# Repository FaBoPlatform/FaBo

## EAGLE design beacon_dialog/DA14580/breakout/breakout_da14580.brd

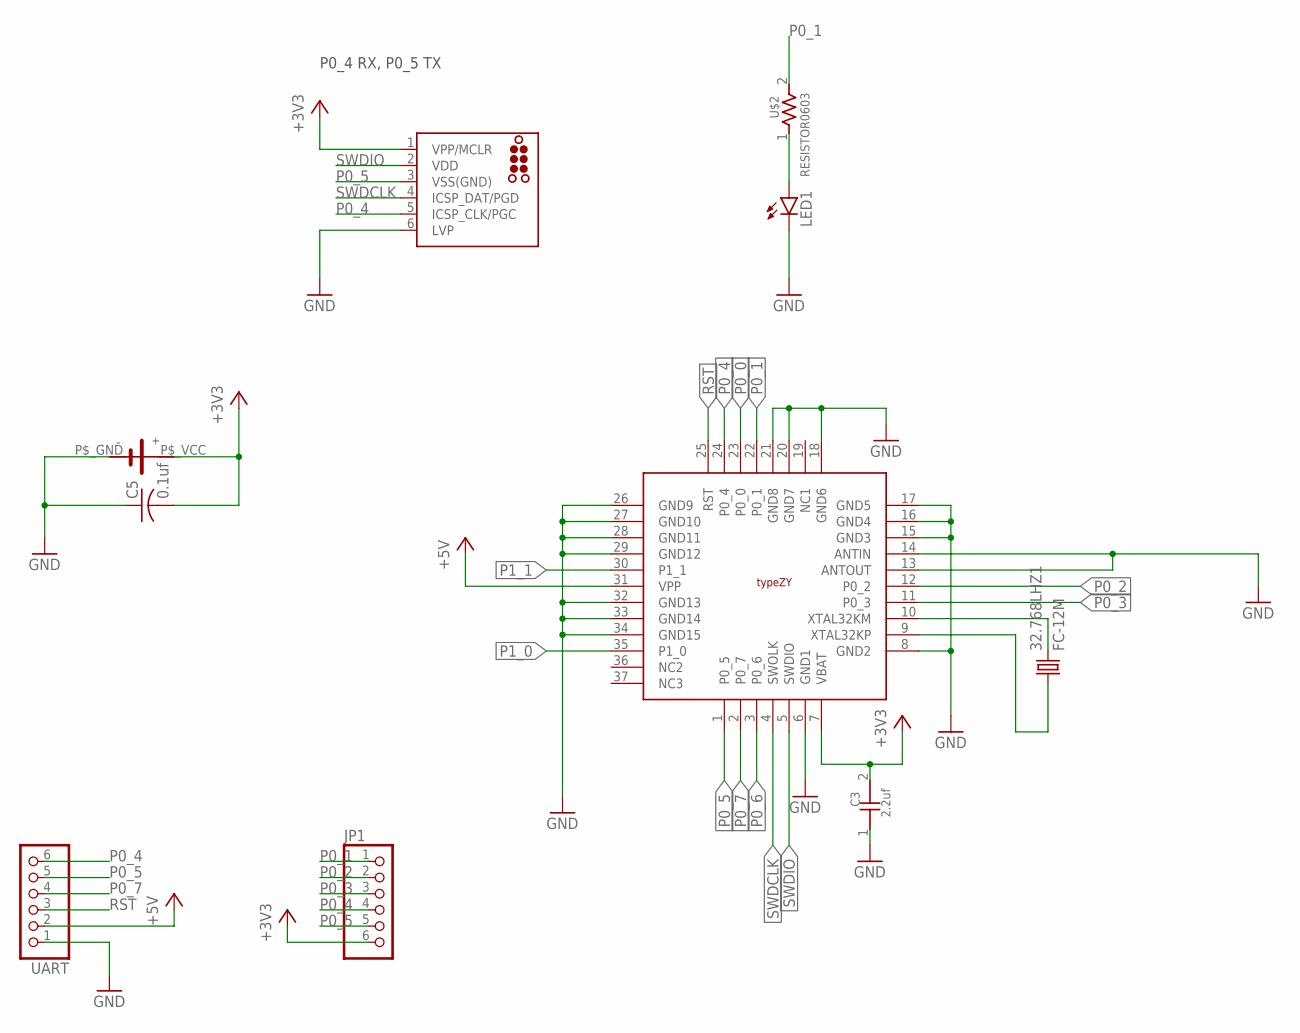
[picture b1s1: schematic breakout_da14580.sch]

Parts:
32.768LHZ1: FC-12M
C3: 2.2uf; 0603
C5: 0.1uf; C0603
J1: TC2030-MCP
JP1: PINHD-1X6; 1X06
LED1: LED-EIA0603; EIA0603-LED
U$1: MURATA-TYPEZY; MURATA_TYPEZY
U$2: RESISTOR0603; 0603
U$3: SMTU2450-BOTTOM-MINI
UART: PINHD-1X6; 1X06

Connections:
+3V3: C3.2, C5.2, J1.1 (VPP/MCLR), JP1.6, U$1.7 (VBAT), U$3.P$_VCC
+5V: U$1.31 (VPP), UART.2
GND: C3.1, C5.1, J1.6 (LVP), LED1.C, U$1.6 (GND1), U$1.8 (GND2), U$1.13 (ANTOUT), U$1.14 (ANTIN), U$1.15 (GND3), U$1.16 (GND4), U$1.17 (GND5), U$1.18 (GND6), U$1.20 (GND7), U$1.21 (GND8), U$1.26 (GND9), U$1.27 (GND10), U$1.28 (GND11), U$1.29 (GND12), U$1.32 (GND13), U$1.33 (GND14), U$1.34 (GND15), U$3.P$_GND, UART.1
unnamed: LED1.A, U$2.1
P0_0: U$1.23 (P0_0)
P0_1: JP1.1, U$1.22 (P0_1), U$2.2
P0_2: JP1.2, U$1.12 (P0_2)
P0_3: JP1.3, U$1.11 (P0_3)
P0_4: J1.5 (ICSP_CLK/PGC), JP1.4, U$1.24 (P0_4), UART.6
P0_5: J1.3 (VSS(GND)), JP1.5, U$1.1 (P0_5), UART.5
P0_6: U$1.3 (P0_6)
P0_7: U$1.2 (P0_7), UART.4
P1_0: U$1.35 (P1_0)
P1_1: U$1.30 (P1_1)
RST: U$1.25 (RST), UART.3
SWDCLK: J1.4 (ICSP_DAT/PGD), U$1.4 (SWOLK)
SWDIO: J1.2 (VDD), U$1.5 (SWDIO)
XTAL32KM: 32.768LHZ1.2, U$1.10 (XTAL32KM)
XTAL32KP: 32.768LHZ1.1, U$1.9 (XTAL32KP)

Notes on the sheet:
P0_4 RX, P0_5 TX

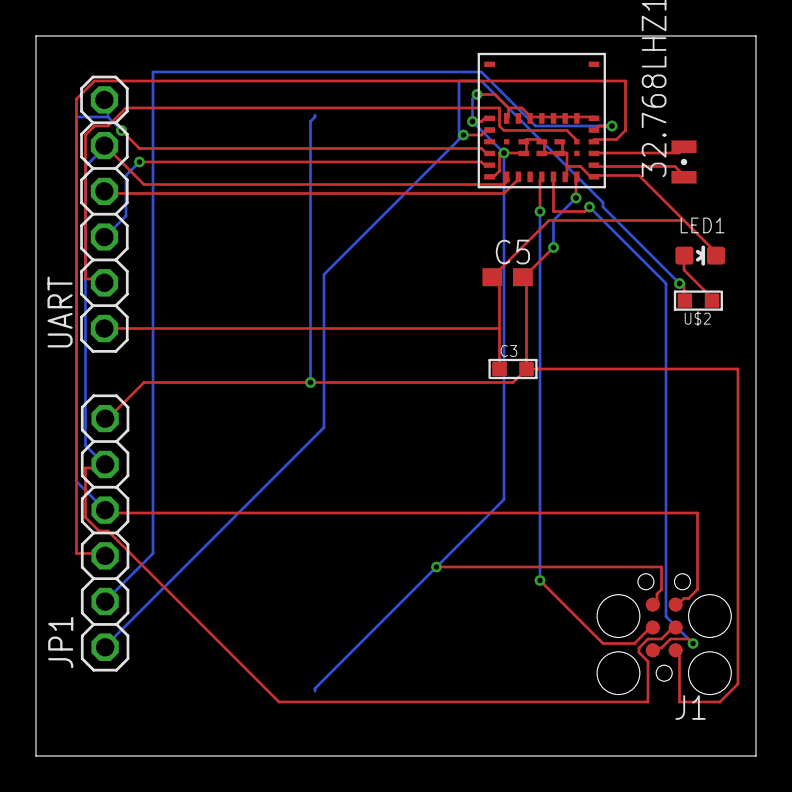
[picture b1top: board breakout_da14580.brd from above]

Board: 2 copper layers, 40.0 x 40.0 mm, 10 parts (0 on the bottom side), 15 nets.

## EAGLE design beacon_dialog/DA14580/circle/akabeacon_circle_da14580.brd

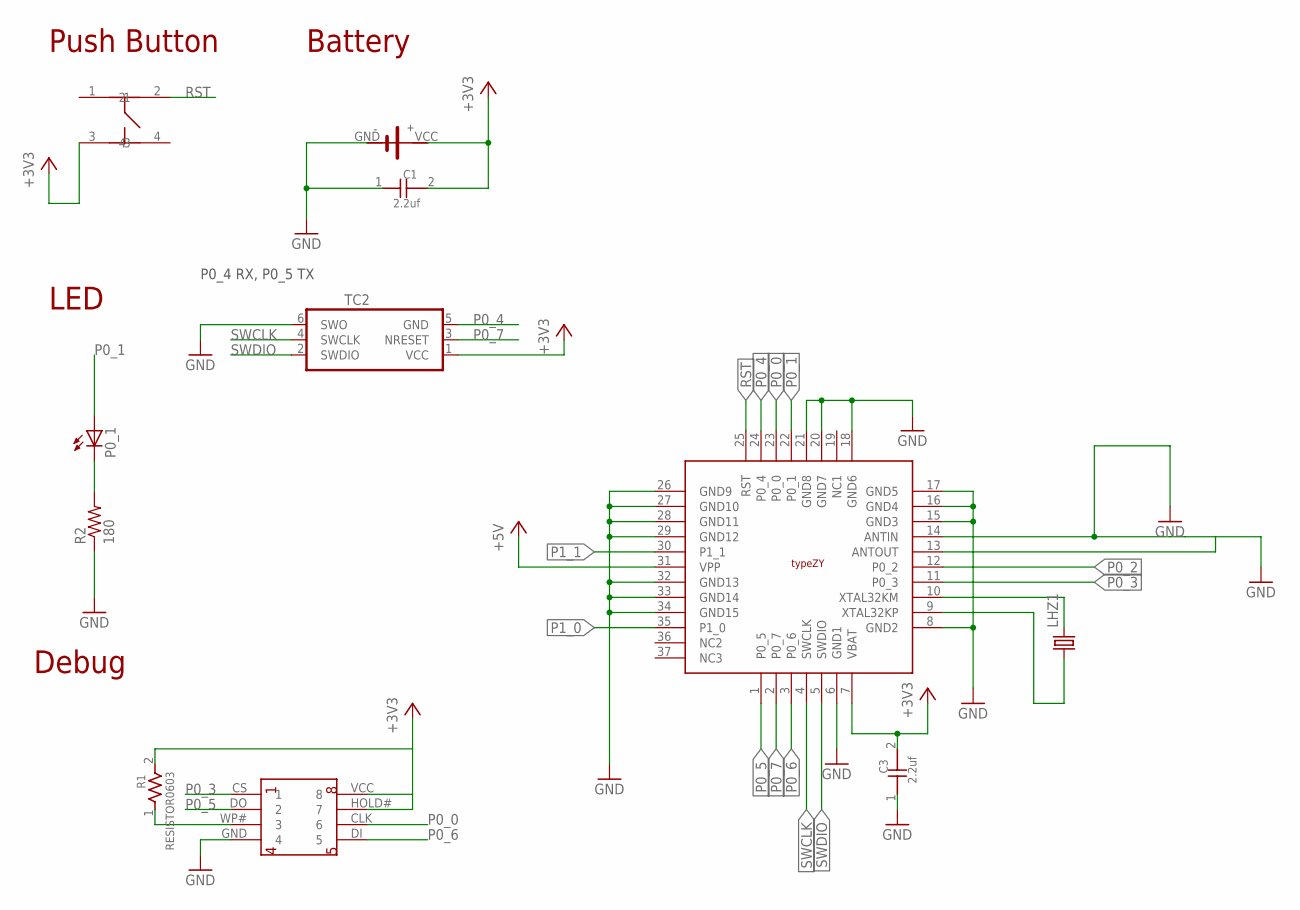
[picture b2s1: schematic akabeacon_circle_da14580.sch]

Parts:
C1, C3: 2.2uf; 0603
LHZ1: FC-12M
P0_1: LEDCHIP-LED0603; CHIP-LED0603
R1: RESISTOR0603; 0603
R2: 180; 0603-RES
TC2: TC2030-IDC-NL
U$1: MURATA-TYPEZY; MURATA_TYPEZY
U$3: CIRCLE-TYPE1; CIRCLE-TYE1-TC2030
U$5: FLASH-MEMORY-2M(WINBOND)
U$7: SWICTH-4P(KMR2); SWITCH-4P(KMR2)

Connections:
+3V3: C1.2, C3.2, R1.2, TC2.1 (VCC), U$1.7 (VBAT), U$3.VCC, U$5.HOLD# (7), U$5.VCC (8), U$7.3
+5V: U$1.31 (VPP)
GND: C1.1, C3.1, R2.1, TC2.6 (SWO), U$1.6 (GND1), U$1.8 (GND2), U$1.14 (ANTIN), U$1.15 (GND3), U$1.16 (GND4), U$1.17 (GND5), U$1.18 (GND6), U$1.20 (GND7), U$1.21 (GND8), U$1.26 (GND9), U$1.27 (GND10), U$1.28 (GND11), U$1.29 (GND12), U$1.32 (GND13), U$1.33 (GND14), U$1.34 (GND15), U$3.GND, U$5.GND (4)
LED1: P0_1.C, R2.2
unnamed: R1.1, U$5.WP# (3)
P0_0: U$1.23 (P0_0), U$5.CLK (6)
P0_1: P0_1.A, U$1.22 (P0_1)
P0_2: U$1.12 (P0_2)
P0_3: U$1.11 (P0_3), U$5.CS (1)
P0_4: TC2.5 (GND), U$1.24 (P0_4)
P0_5: U$1.1 (P0_5), U$5.DO (2)
P0_6: U$1.3 (P0_6), U$5.DI (5)
P0_7: TC2.3 (NRESET), U$1.2 (P0_7)
P1_0: U$1.35 (P1_0)
P1_1: U$1.30 (P1_1)
RST: U$1.25 (RST), U$7.2
SWCLK: TC2.4 (SWCLK), U$1.4 (SWCLK)
SWDIO: TC2.2 (SWDIO), U$1.5 (SWDIO)
XTAL32KM: LHZ1.2, U$1.10 (XTAL32KM)
XTAL32KP: LHZ1.1, U$1.9 (XTAL32KP)

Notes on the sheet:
Battery
Push Button
Debug
LED
P0_4 RX, P0_5 TX

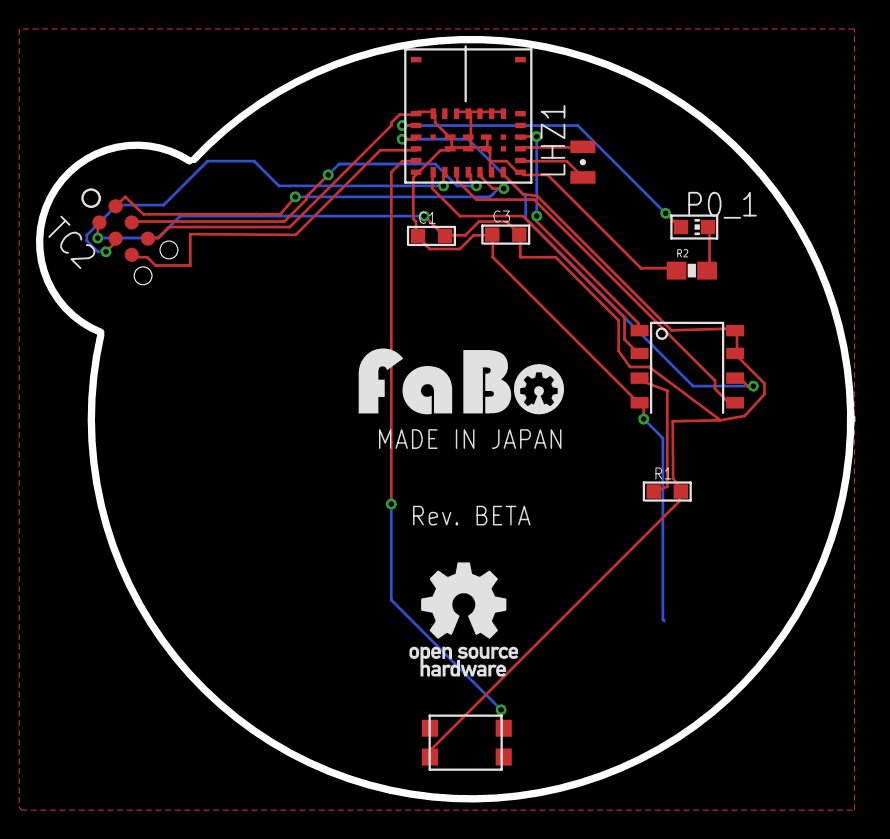
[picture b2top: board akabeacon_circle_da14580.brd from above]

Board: 2 copper layers, 13 parts (0 on the bottom side), 16 nets.

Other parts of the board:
U$2: LOGO_FABO_M
U$6: LOGO_OSHW_T_M

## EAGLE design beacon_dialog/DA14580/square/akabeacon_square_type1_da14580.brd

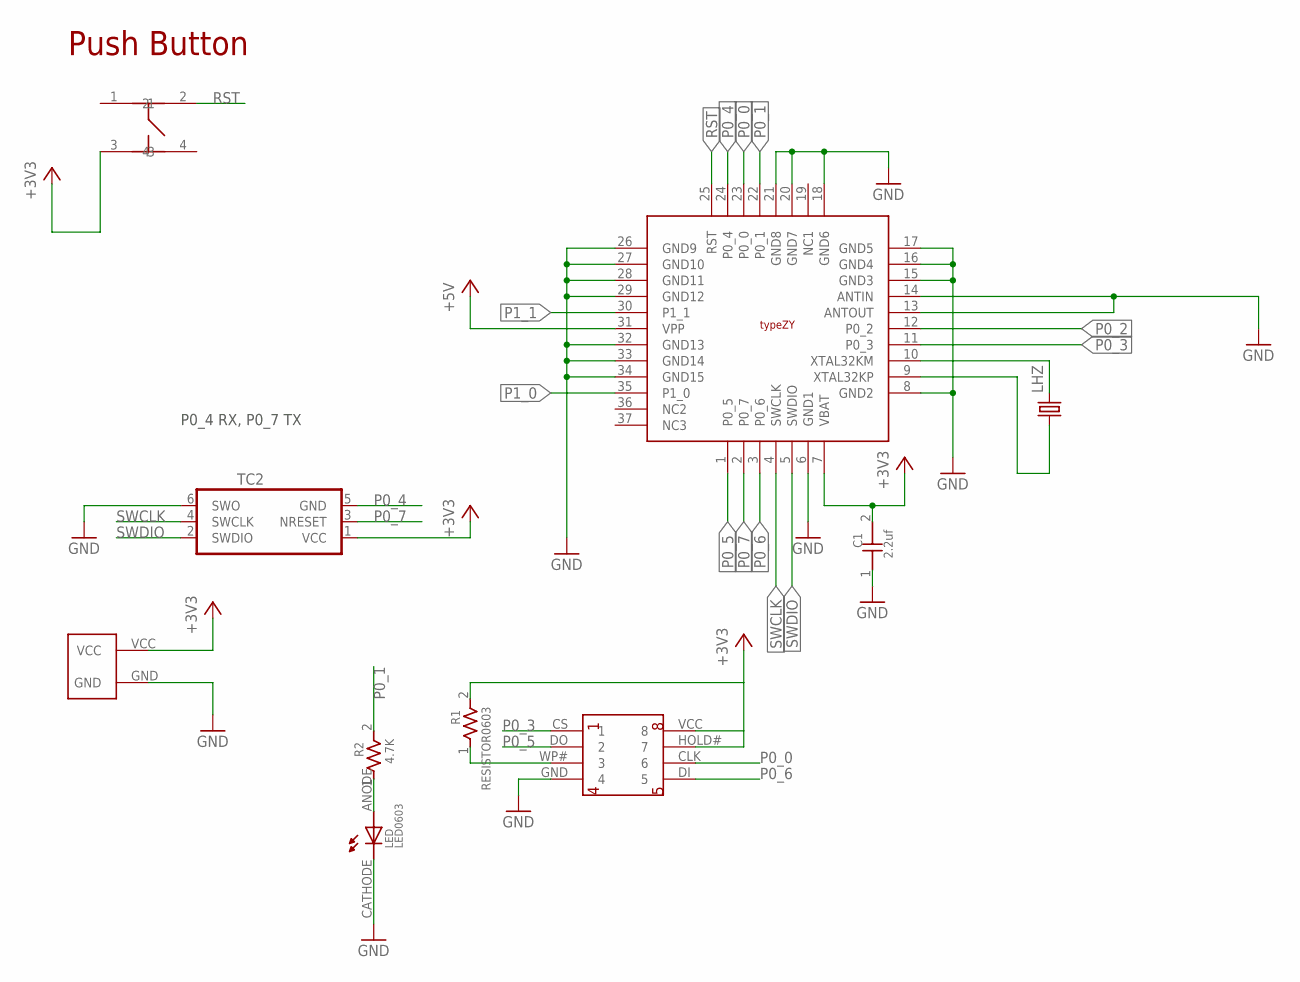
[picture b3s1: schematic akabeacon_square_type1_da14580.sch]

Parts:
C1: 2.2uf; 0603
LED: LED0603; 0603
LHZ: FC-12M
R1: RESISTOR0603; 0603
R2: 4.7K; 0603
TC2: TC2030-IDC-NL
U$2: SQUARE-TYPE1; SQUARE-TYPE1-TC2030
U$3: FLASH-MEMORY-2M(WINBOND)
U$7: SWICTH-4P(KMR2); SWITCH-4P(KMR2)
U$9: MURATA-TYPEZY; MURATA_TYPEZY

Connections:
+3V3: C1.2, R1.2, TC2.1 (VCC), U$2.VCC, U$3.HOLD# (7), U$3.VCC (8), U$7.3, U$9.7 (VBAT)
+5V: U$9.31 (VPP)
GND: C1.1, LED.CATHODE, TC2.6 (SWO), U$2.GND, U$3.GND (4), U$9.6 (GND1), U$9.8 (GND2), U$9.13 (ANTOUT), U$9.14 (ANTIN), U$9.15 (GND3), U$9.16 (GND4), U$9.17 (GND5), U$9.18 (GND6), U$9.20 (GND7), U$9.21 (GND8), U$9.26 (GND9), U$9.27 (GND10), U$9.28 (GND11), U$9.29 (GND12), U$9.32 (GND13), U$9.33 (GND14), U$9.34 (GND15)
unnamed: R1.1, U$3.WP# (3)
unnamed: LED.ANODE, R2.1
P0_0: U$3.CLK (6), U$9.23 (P0_0)
P0_1: R2.2, U$9.22 (P0_1)
P0_2: U$9.12 (P0_2)
P0_3: U$3.CS (1), U$9.11 (P0_3)
P0_4: TC2.5 (GND), U$9.24 (P0_4)
P0_5: U$3.DO (2), U$9.1 (P0_5)
P0_6: U$3.DI (5), U$9.3 (P0_6)
P0_7: TC2.3 (NRESET), U$9.2 (P0_7)
P1_0: U$9.35 (P1_0)
P1_1: U$9.30 (P1_1)
RST: U$7.2, U$9.25 (RST)
SWCLK: TC2.4 (SWCLK), U$9.4 (SWCLK)
SWDIO: TC2.2 (SWDIO), U$9.5 (SWDIO)
XTAL32KM: LHZ.2, U$9.10 (XTAL32KM)
XTAL32KP: LHZ.1, U$9.9 (XTAL32KP)

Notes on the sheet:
Push Button
P0_4 RX, P0_7 TX

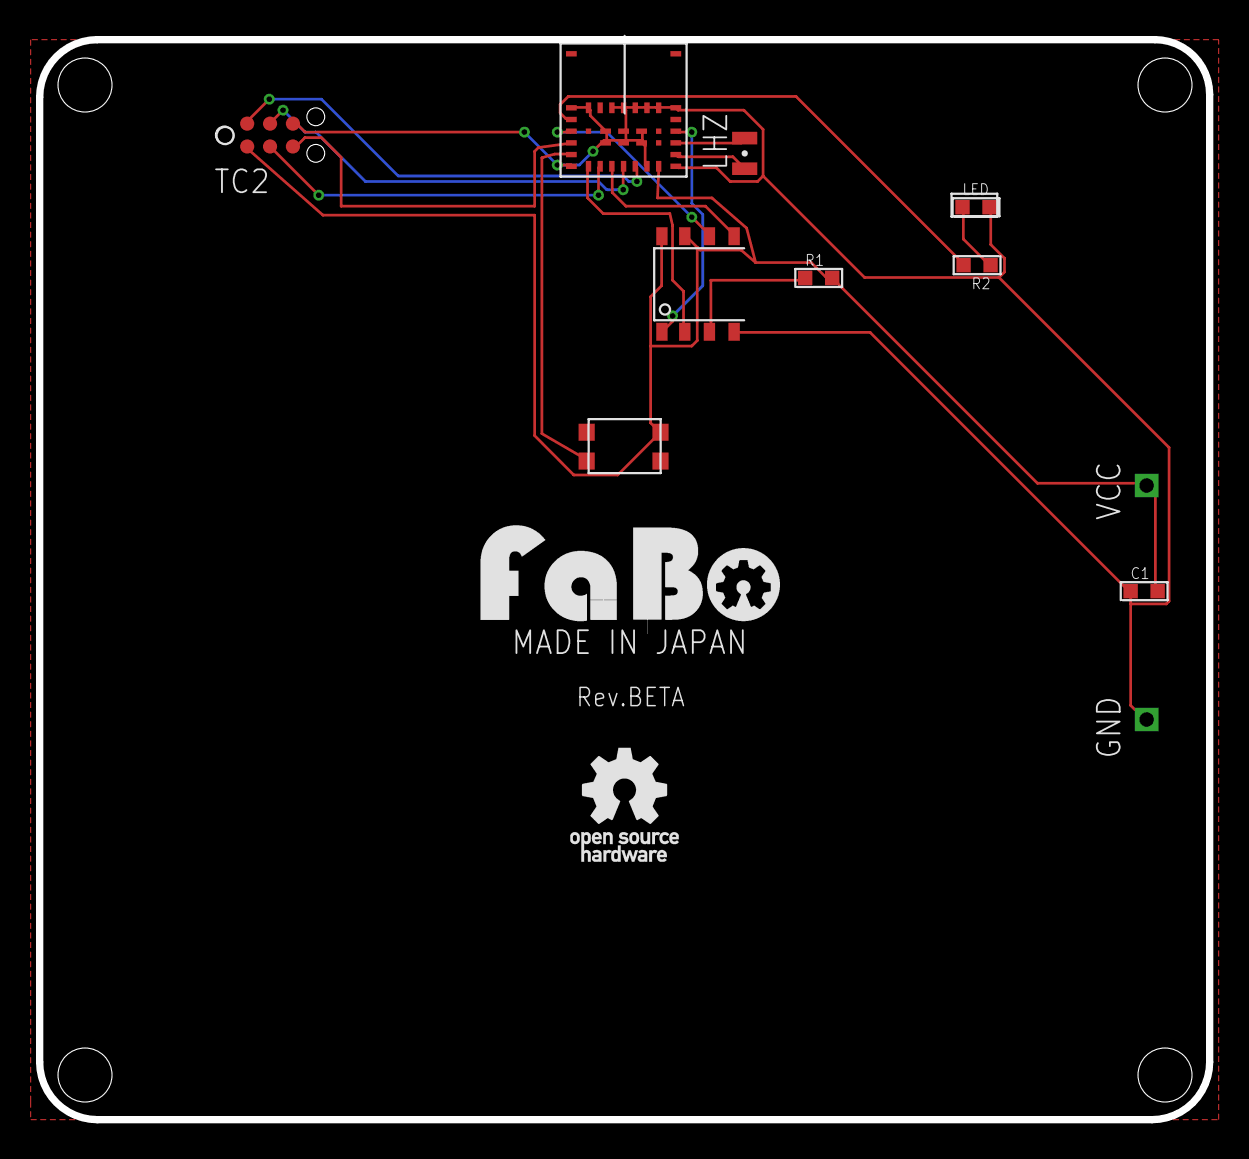
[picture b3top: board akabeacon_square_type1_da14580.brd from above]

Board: 2 copper layers, 65.0 x 60.0 mm, 10 parts (0 on the bottom side), 16 nets.

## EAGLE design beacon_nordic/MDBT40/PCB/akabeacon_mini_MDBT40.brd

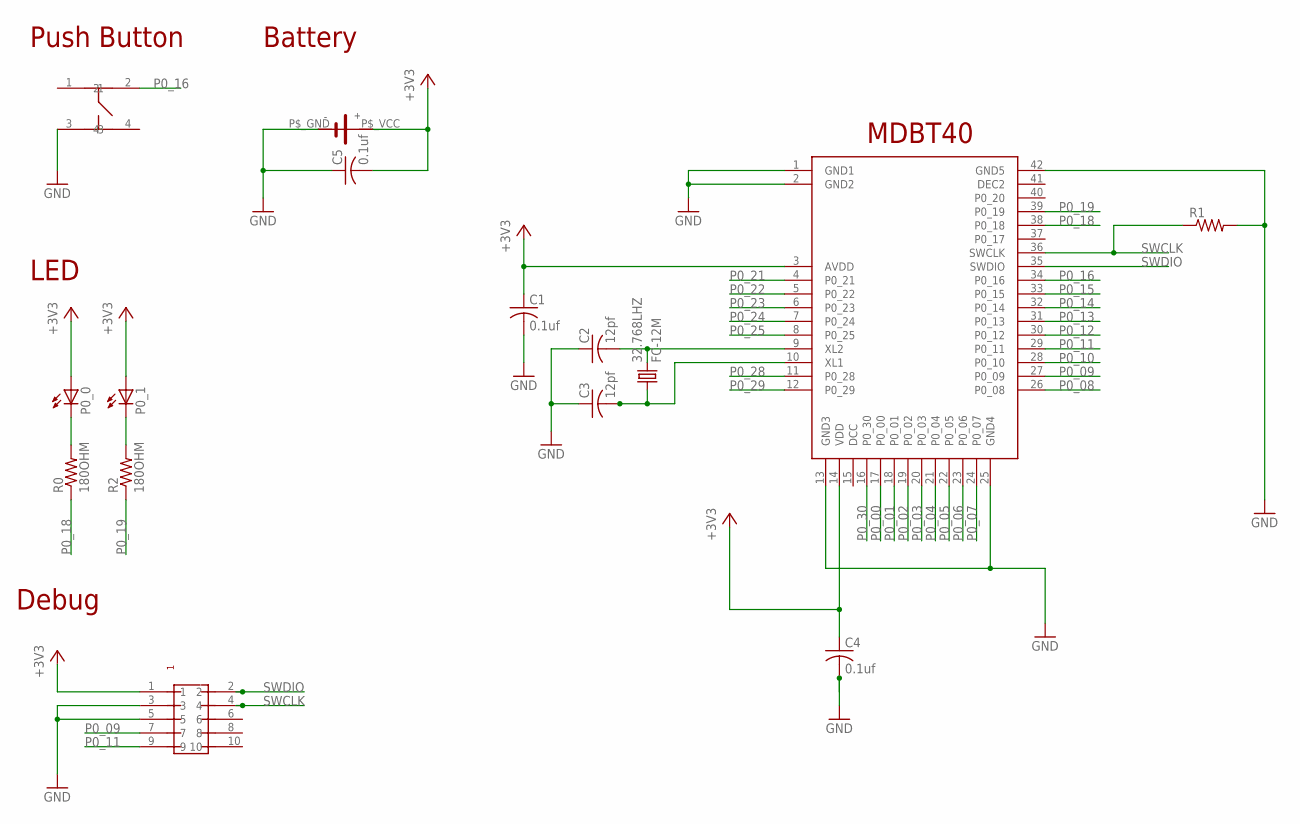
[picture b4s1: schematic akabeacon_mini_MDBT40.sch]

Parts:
32.768LHZ: FC-12M
C1, C4, C5: 0.1uf; C0603
C2, C3: 12pf; C0603
P0_0, P0_1: LEDCHIP-LED0603; CHIP-LED0603
R0, R2: 180OHM; 0603-RES
R1: R-US_R0603; R0603
U$1: RAYTAC-MDBT40
U$2: PIN-HEADER-SMT(1.27MM)2X5
U$3: SMTU2450-BOTTOM-MINI
U$5: SWICTH-4P(KMR2); SWITCH-4P(KMR2)

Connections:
+3V3: C1.1, C4.1, C5.2, P0_0.A, P0_1.A, U$1.3 (AVDD), U$1.14 (VDD), U$2.1, U$3.P$_VCC
GND: C1.2, C2.1, C3.1, C4.2, C5.1, R1.2, U$1.1 (GND1), U$1.2 (GND2), U$1.13 (GND3), U$1.25 (GND4), U$1.42 (GND5), U$2.3, U$2.5, U$3.P$_GND, U$5.3
LED1: P0_0.C, R0.2
unnamed: P0_1.C, R2.2
unnamed: 32.768LHZ.2, C2.2, U$1.9 (XL2)
unnamed: 32.768LHZ.1, C3.2, U$1.10 (XL1)
P0_00: U$1.17 (P0_00)
P0_01: U$1.18 (P0_01)
P0_02: U$1.19 (P0_02)
P0_03: U$1.20 (P0_03)
P0_04: U$1.21 (P0_04)
P0_05: U$1.22 (P0_05)
P0_06: U$1.23 (P0_06)
P0_07: U$1.24 (P0_07)
P0_08: U$1.26 (P0_08)
P0_09: U$1.27 (P0_09), U$2.7
P0_10: U$1.28 (P0_10)
P0_11: U$1.29 (P0_11), U$2.9
P0_12: U$1.30 (P0_12)
P0_13: U$1.31 (P0_13)
P0_14: U$1.32 (P0_14)
P0_15: U$1.33 (P0_15)
P0_16: U$1.34 (P0_16), U$5.2
P0_18: R0.1, U$1.38 (P0_18)
P0_19: R2.1, U$1.39 (P0_19)
P0_21: U$1.4 (P0_21)
P0_22: U$1.5 (P0_22)
P0_23: U$1.6 (P0_23)
P0_24: U$1.7 (P0_24)
P0_25: U$1.8 (P0_25)
P0_28: U$1.11 (P0_28)
P0_29: U$1.12 (P0_29)
P0_30: U$1.16 (P0_30)
SWCLK: R1.1, U$1.36 (SWCLK), U$2.4
SWDIO: U$1.35 (SWDIO), U$2.2

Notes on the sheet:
Battery
Push Button
Debug
MDBT40
LED

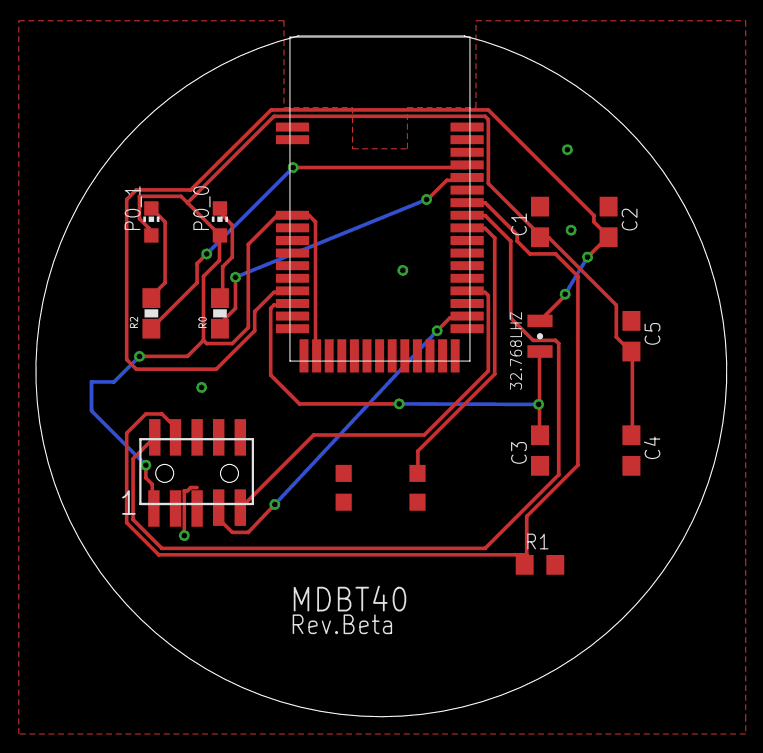
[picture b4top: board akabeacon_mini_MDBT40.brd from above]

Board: 2 copper layers, 38.4 x 37.8 mm, 15 parts (0 on the bottom side), 13 nets.

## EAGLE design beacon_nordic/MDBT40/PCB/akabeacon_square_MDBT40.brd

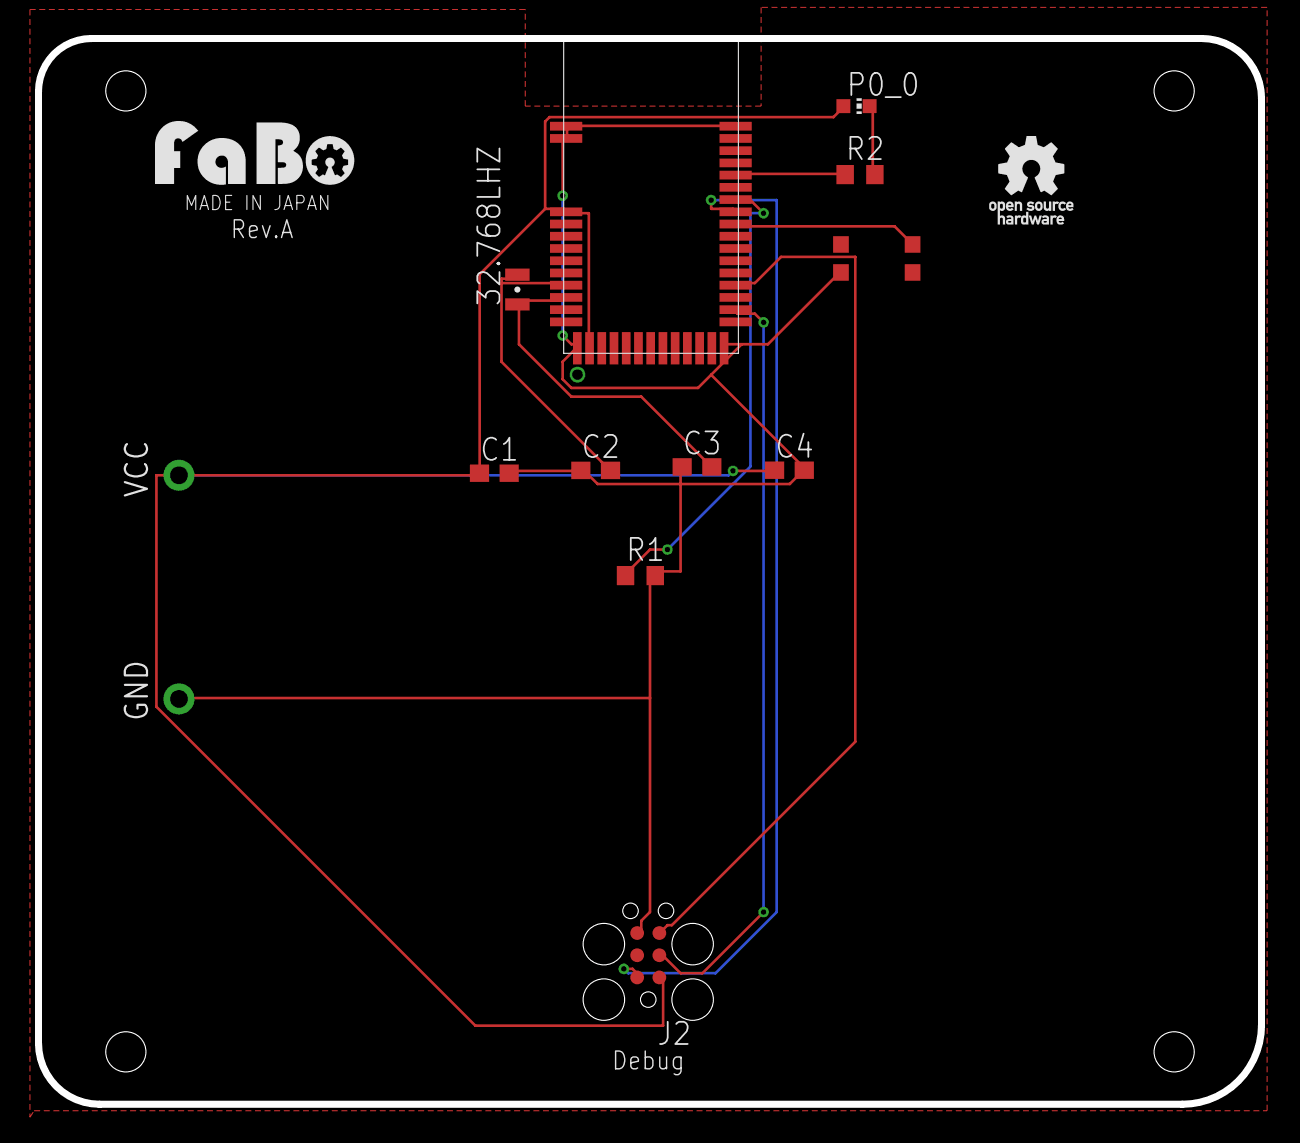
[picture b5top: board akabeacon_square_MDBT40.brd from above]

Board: 2 copper layers, 70.0 x 61.0 mm, 15 parts (0 on the bottom side), 11 nets.

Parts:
32.768LHZ: FC-12M
C1, C4: 0.1uf; C0603
C2, C3: 12pf; C0603
GND: 1X01-CLEANBIG
J2: TC2030-MCP
P0_0: CHIP-LED0603
R1, R2: R0603
U$2: LOGO_FABO_M
U$3: RAYTAC-MDBT40
U$4: LOGO_OSHW_T_M
U$6: SWICTH-4P(KMR2); SWITCH-4P(KMR2)
VCC: 1X01-CLEANBIG

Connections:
+3V3: C1.1, C4.1, J2.1, P0_0.A, U$3.3, U$3.14, VCC.1
GND: C1.2, C2.1, C3.1, C4.2, GND.1, J2.6, R1.2, U$3.1, U$3.2, U$3.13, U$3.25, U$3.42, U$6.3
LED1: P0_0.C, R2.2
unnamed: 32.768LHZ.2, C2.2, U$3.9
unnamed: 32.768LHZ.1, C3.2, U$3.10
P0_09: J2.3, U$3.27
P0_11: J2.5, U$3.29
P0_16: U$3.34, U$6.2
P0_18: R2.1, U$3.38
SWCLK: R1.1, U$3.36
SWDIO: J2.2, U$3.35

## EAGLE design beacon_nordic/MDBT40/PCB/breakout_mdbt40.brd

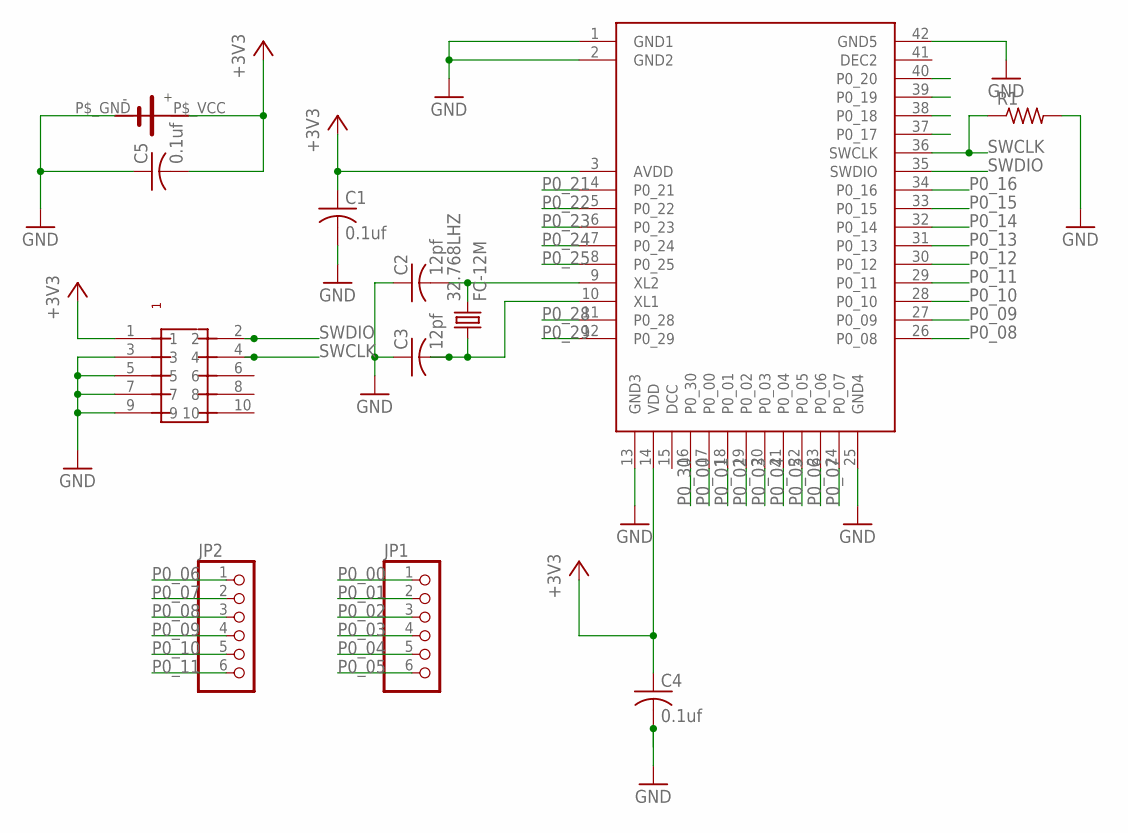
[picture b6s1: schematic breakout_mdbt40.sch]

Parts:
32.768LHZ: FC-12M
C1, C4, C5: 0.1uf; C0603
C2, C3: 12pf; C0603
JP1, JP2: PINHD-1X6; 1X06
R1: R-US_R0603; R0603
U$1: RAYTAC-MDBT40
U$2: PIN-HEADER-SMT(1.27MM)2X5
U$3: SMTU2450-BOTTOM-MINI

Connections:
+3V3: C1.1, C4.1, C5.2, U$1.3 (AVDD), U$1.14 (VDD), U$2.1, U$3.P$_VCC; also elsewhere on the board
GND: C1.2, C2.1, C3.1, C4.2, C5.1, R1.2, U$1.1 (GND1), U$1.2 (GND2), U$1.13 (GND3), U$1.25 (GND4), U$1.42 (GND5), U$2.3, U$2.5, U$2.7, U$2.9, U$3.P$_GND; also elsewhere on the board
unnamed: 32.768LHZ.2, C2.2, U$1.9 (XL2)
unnamed: 32.768LHZ.1, C3.2, U$1.10 (XL1)
P0_00: JP1.1, U$1.17 (P0_00)
P0_01: JP1.2, U$1.18 (P0_01)
P0_02: JP1.3, U$1.19 (P0_02)
P0_03: JP1.4, U$1.20 (P0_03)
P0_04: JP1.5, U$1.21 (P0_04)
P0_05: JP1.6, U$1.22 (P0_05)
P0_06: JP2.1, U$1.23 (P0_06)
P0_07: JP2.2, U$1.24 (P0_07)
P0_08: JP2.3, U$1.26 (P0_08)
P0_09: JP2.4, U$1.27 (P0_09); also elsewhere on the board
P0_10: JP2.5, U$1.28 (P0_10)
P0_11: JP2.6, U$1.29 (P0_11); also elsewhere on the board
P0_12: U$1.30 (P0_12)
P0_13: U$1.31 (P0_13)
P0_14: U$1.32 (P0_14)
P0_15: U$1.33 (P0_15)
P0_16: U$1.34 (P0_16)
P0_21: U$1.4 (P0_21)
P0_22: U$1.5 (P0_22)
P0_23: U$1.6 (P0_23)
P0_24: U$1.7 (P0_24)
P0_25: U$1.8 (P0_25)
P0_28: U$1.11 (P0_28)
P0_29: U$1.12 (P0_29)
P0_30: U$1.16 (P0_30)
SWCLK: R1.1, U$1.36 (SWCLK), U$2.4
SWDIO: U$1.35 (SWDIO), U$2.2; also elsewhere on the board

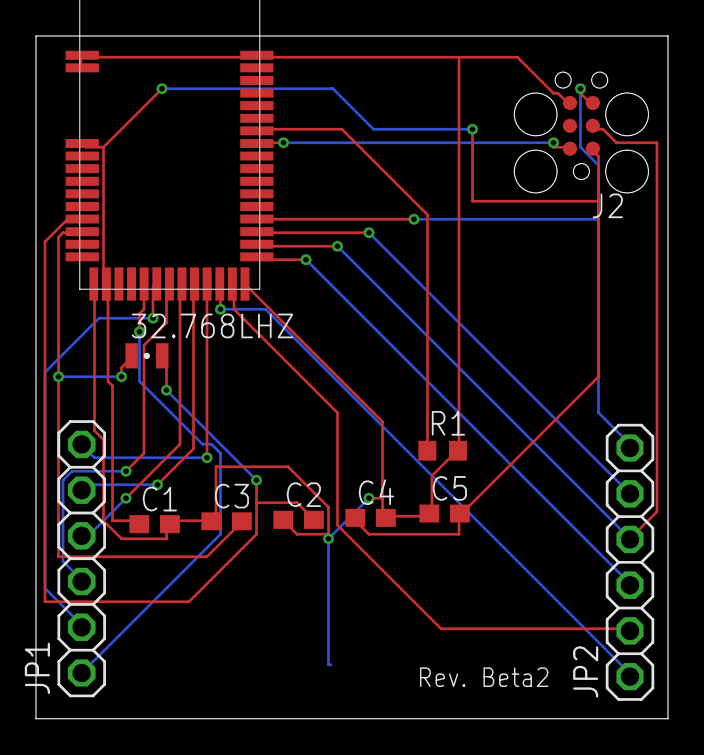
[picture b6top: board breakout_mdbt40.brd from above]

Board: 2 copper layers, 35.1 x 37.9 mm, 12 parts (0 on the bottom side), 18 nets.

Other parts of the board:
J2: TC2030-MCP

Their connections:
+3V3: J2.1; also elsewhere on the board
GND: J2.6; also elsewhere on the board
P0_09: J2.3; also elsewhere on the board
P0_11: J2.5; also elsewhere on the board
SWDIO: J2.2; also elsewhere on the board

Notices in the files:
parts and their libraries:
tag-connect: ©2009 ROFA.cz - modified and updated by Robert Darlington ‹rdarlington@gmail.com›
SparkFun: Licensing: CC v3.0 Share-Alike You are welcome to use this library for commercial purposes.
